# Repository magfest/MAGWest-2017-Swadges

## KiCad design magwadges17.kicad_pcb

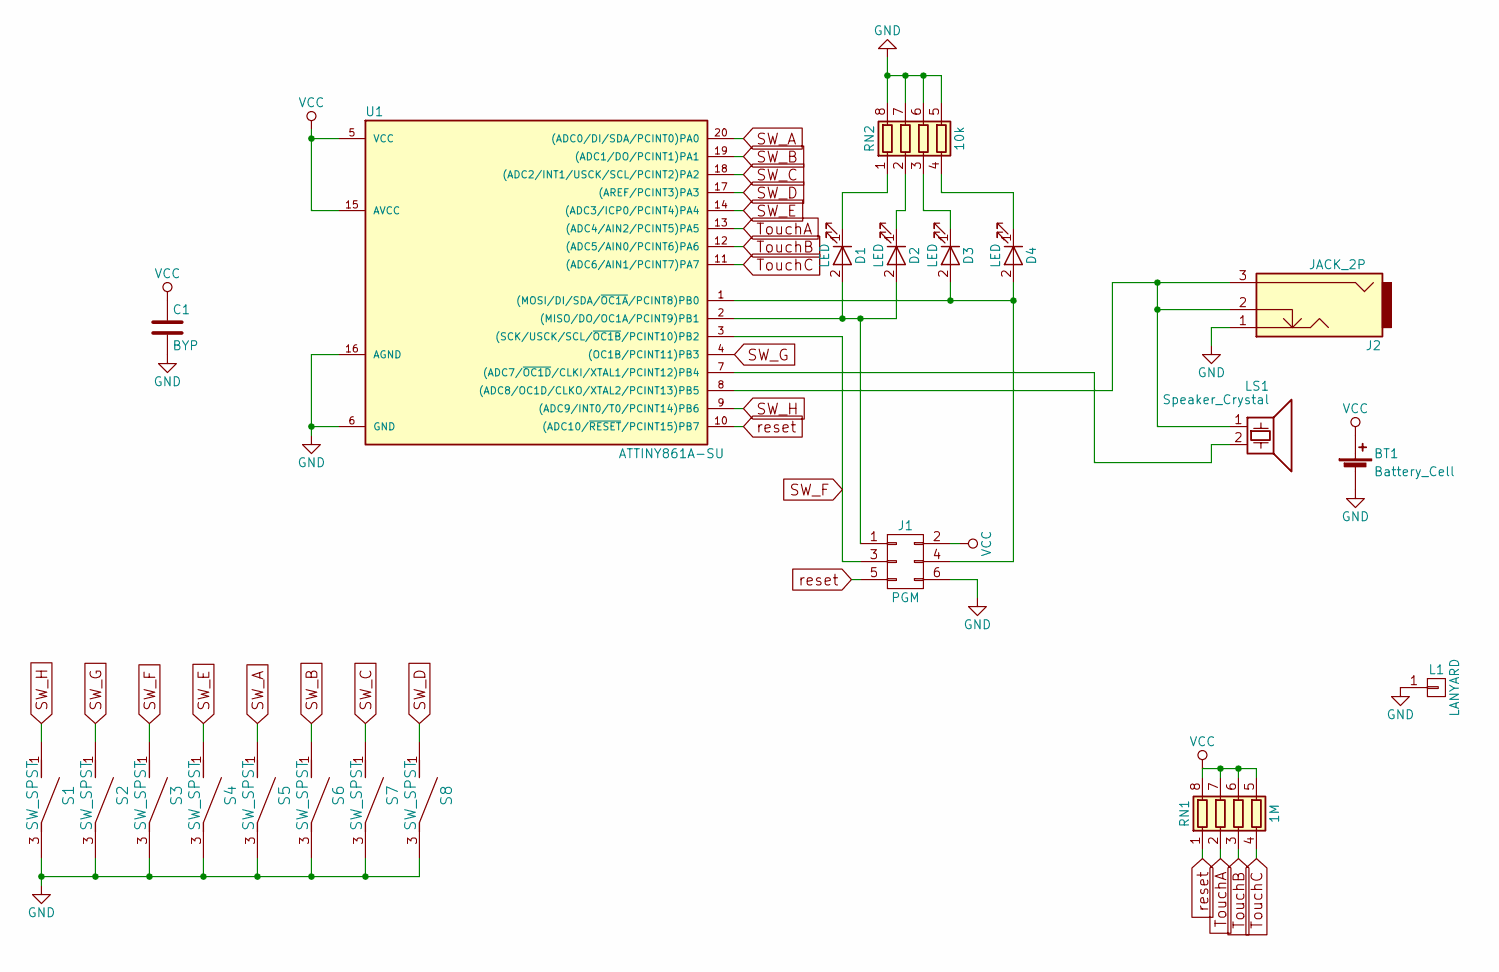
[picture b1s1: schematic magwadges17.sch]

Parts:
BT1: Battery_Cell; S8211-45R
C1: BYP; SM0805
D1, D2, D3, D4: LED; SM0805
J1: PGM; Pin_Header_Straight_2x03_Pitch2.54mm_SMD
J2: JACK_2P; SJ-252X-SMT
L1: LANYARD; 1pin
LS1: Speaker_Crystal; PS1740P02CE
RN1: 1M; NETWORK1206
RN2: 10k; NETWORK1206
S1, S2, S3, S4, S5, S6, S7, S8: SW_SPST; PTS645
U1: ATTINY861A-SU; SOIC-20W_7.5x12.8mm_Pitch1.27mm

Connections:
GND: BT1.2 (-), C1.2, J1.6, J2.1, L1.1, RN2.5 (R4.2), RN2.6 (R3.2), RN2.7 (R2.2), RN2.8 (R1.2), S1.3, S2.3, S3.3, S4.3, S5.3, S6.3, S7.3, S8.3, U1.6 (GND), U1.16 (AGND)
unnamed: D1.1 (K), RN2.1 (R1.1)
unnamed: D1.2 (A), D2.2 (A), J1.1, U1.2 ((MISO/DO/OC1A/PCINT9)PB1)
unnamed: D2.1 (K), RN2.2 (R2.1)
unnamed: D3.1 (K), RN2.3 (R3.1)
unnamed: D3.2 (A), D4.2 (A), J1.4, U1.1 ((MOSI/DI/SDA/~OC1A~/PCINT8)PB0)
unnamed: D4.1 (K), RN2.4 (R4.1)
unnamed: J2.2, J2.3, LS1.1, U1.8 ((ADC8/OC1D/CLKO/XTAL2/PCINT13)PB5)
unnamed: LS1.2, U1.7 ((ADC7/~OC1D~/CLKI/XTAL1/PCINT12)PB4)
SW_A: S5.1, U1.20 ((ADC0/DI/SDA/PCINT0)PA0)
SW_B: S6.1, U1.19 ((ADC1/DO/PCINT1)PA1)
SW_C: S7.1, U1.18 ((ADC2/INT1/USCK/SCL/PCINT2)PA2)
SW_D: S8.1, U1.17 ((AREF/PCINT3)PA3)
SW_E: S4.1, U1.14 ((ADC3/ICP0/PCINT4)PA4)
SW_F: J1.3, S3.1, U1.3 ((SCK/USCK/SCL/~OC1B~/PCINT10)PB2)
SW_G: S2.1, U1.4 ((OC1B/PCINT11)PB3)
SW_H: S1.1, U1.9 ((ADC9/INT0/T0/PCINT14)PB6)
TouchA: RN1.2 (R2.1), U1.13 ((ADC4/AIN2/PCINT5)PA5)
TouchB: RN1.3 (R3.1), U1.12 ((ADC5/AIN0/PCINT6)PA6)
TouchC: RN1.4 (R4.1), U1.11 ((ADC6/AIN1/PCINT7)PA7)
VCC: BT1.1 (+), C1.1, J1.2, RN1.5 (R4.2), RN1.6 (R3.2), RN1.7 (R2.2), RN1.8 (R1.2), U1.5 (VCC), U1.15 (AVCC)
reset: J1.5, RN1.1 (R1.1), U1.10 ((ADC10/~RESET~/PCINT15)PB7)

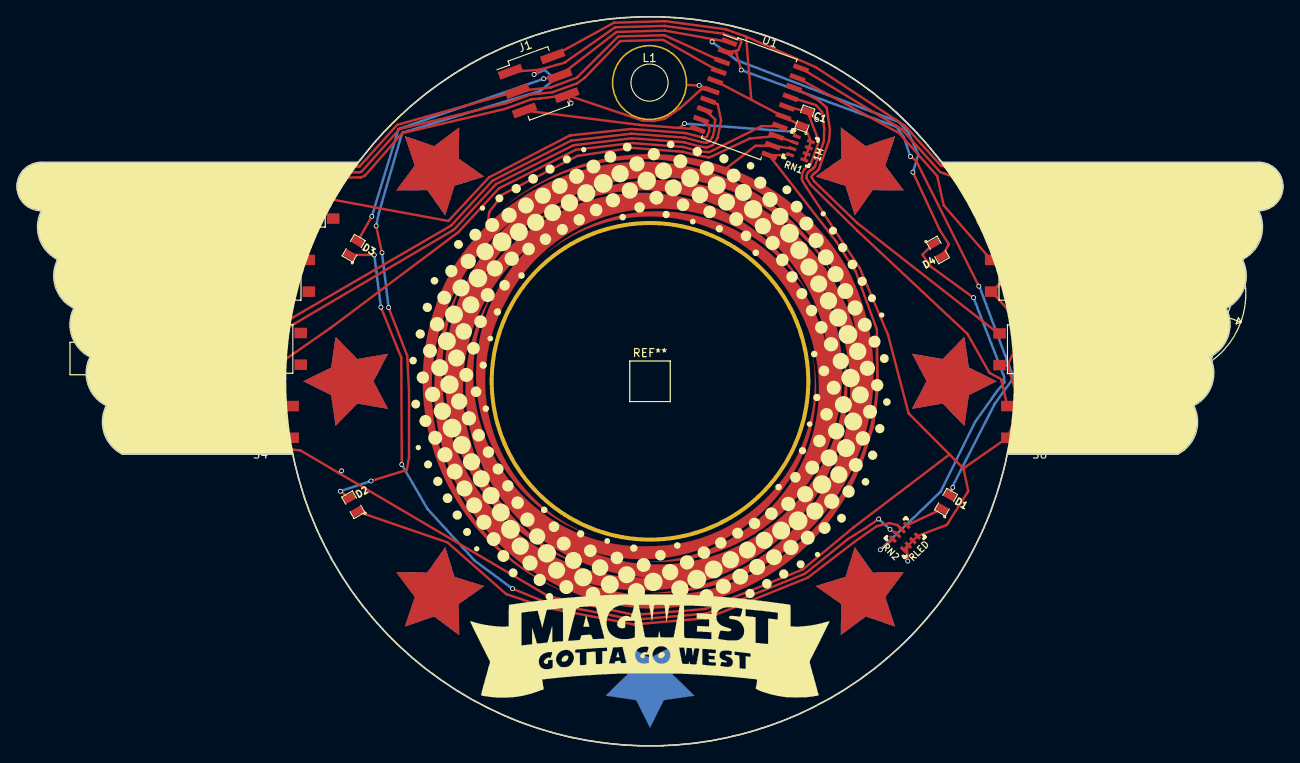
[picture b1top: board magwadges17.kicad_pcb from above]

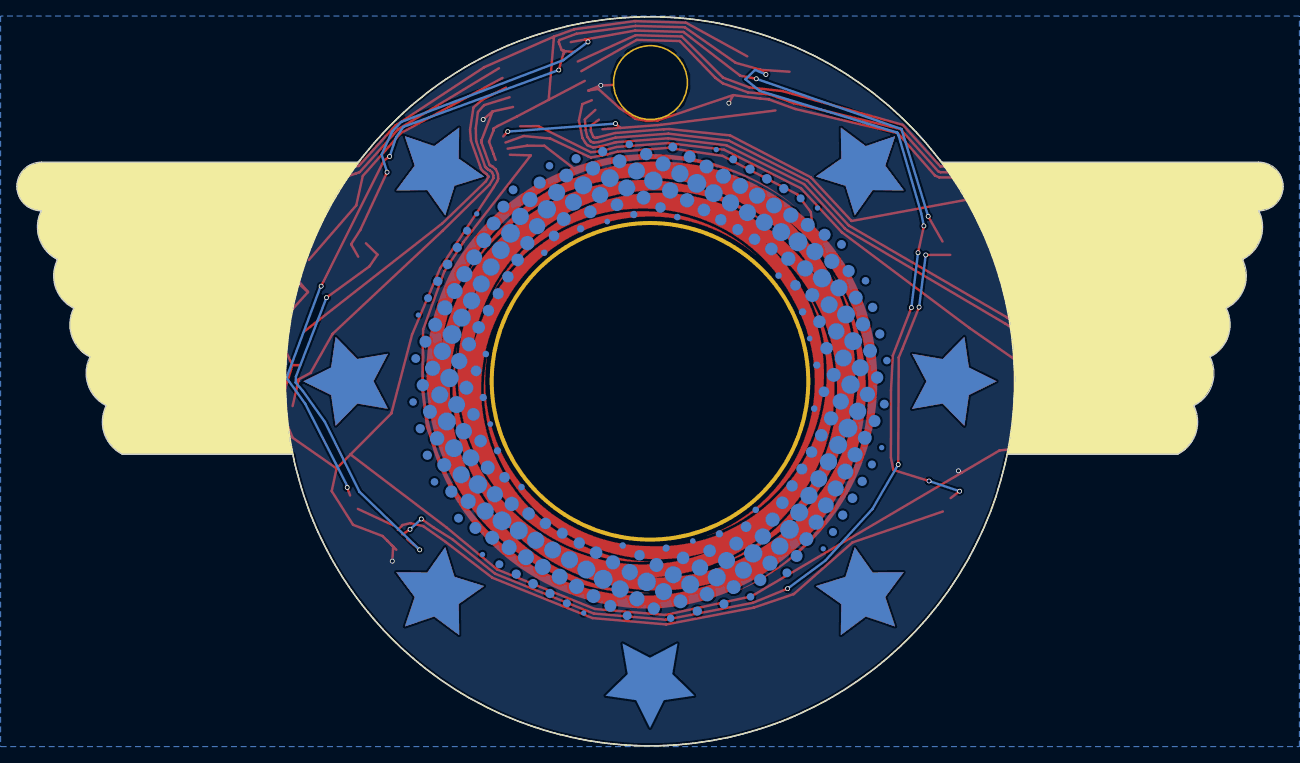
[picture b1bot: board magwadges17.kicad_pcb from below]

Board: 2 copper layers, 156.0 x 89.8 mm, 47 parts (14 on the bottom side), 22 nets.

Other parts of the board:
G0, G1, G2, G4, G4#2, G5, G6, G7, G8, G9, G11, G12, G13: LOGO; test_star4
G14, G15, G16, G18, G18#2, G19, G20, G21, G22, G23, G25, G26, G27: LOGO; test_star4_copper

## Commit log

2017-07-28 Updated schematic
2017-07-31 single layer in
2017-07-31 Fixed layout of battery holder and headphone jack
2017-07-31 add centerspin tool
2017-07-31 Update center spinner
2017-07-31 Update wadges
2017-08-03 Update design
2017-08-04 Update with halftone
2017-08-04 Update design with halftone, etc.
2017-08-04 err apparently forgot tos ave acutal pcb
2017-08-10 update!
2017-08-10 update plots rel
2017-08-10 final plots as they were sent.
2017-08-10 try this, as an alternative
2017-08-10 Revert "final plots as they were sent."
    This reverts commit bfd323c62603574740bf4a4b772e69891fb19e77.
2017-08-10 Update plots as sent.
2017-08-19 Added stupid button code and almost working touch sensing
2017-08-19 Added charles' code
2017-08-19 add test firmware from Friday night. Still needs synchronization.
2017-08-20 I will get a prize if I ge this working, right?
2017-08-20 getting much closer!
2017-08-20 Almost perfect!
2017-08-20 ACTUAL TEST!
2017-08-21 Functionality! sweet sweet functionality.
2017-08-21 Rings!
2017-08-21 Yay! Now operating with a budget of 0.7mA when idle.
2017-08-21 OK, I think this is it for my test firmware
